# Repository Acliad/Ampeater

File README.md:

# Overview
This project is a 50 W electronic load. The table below outlines the basic specs for the load.

| Description                                 | Spec               |
|---------------------------------------------|--------------------|
| Supply Voltage                              | 12 V               |
| Slew Rate                                   | 10 A/µs        |
| Maximum Current                             | 10 A               |
| Maximum Power Dissipation                   | 50 W               |
| Program Resolution (low range / high range) | 1 mA / 10 mA       |
| Program Accuracy                            | 0.2% $\pm$ 0.2% FS |
| Maximum Overshoot                           | 1%                 |
| Measurement Readout Accuracy                | 0.2% $\pm$ 0.2% FS |

The primary challenge with designing an electronic load is to making it stable over a wide range of load currents and input conditions. This challenges becomes worse when the design demands a fast rise time. The target slew rate for this load is 10 A/µs, which is quite fast. In comparison, the [Keysight EL34243A](https://www.keysight.com/zz/en/assets/3120-1430/data-sheets/EL30000-Series.pdf) has a slew rate of about 5 A/µs. 

This challenge is two-fold. The initial and obvious challenge is the control loop, which is discussed in detail in the [Theory Of Operation](#theory-of-operation) section. Simply, this requires proper compensation to maintain stability and rise time. The more nefarious issue is the issue of input impedance, largely due to the inductance of the wires connecting the load to the source being tested. This inductance is, in general, not known and can vary widely, in the range of 50 nH to 2 uH between short, heavy gauge wire and garden-variety banana cables. This inductance has a large affect on the control loop and can significantly change the rise time and stability of the load. 

Because the current level and slew rate are so large, the slew rate and overshoot specs are defined to be valid for input inductances in the range of 100 nH–roughly 10 cm of 12 AWG wire. This was the assumed input inductance during the design stage. 

# Design and Simulation
## The Control Loop
Figure 1 shows the main control circuit. The main compensation components have been highlighted. Q201 and gate resistors are used to switch the current range between 1 A and 10 A. For this analysis, assume either R211+R212 OR R214 is connected. R202 isolates the output of the opamp from the gate capacitance, which is required for stability. This compensator is known as a [*Type III compensator*](https://www.ti.com/seclit/ml/slup340/slup340.pdf). There are two compensators, each designed to sink up to 0.5/5.0 A. This is done to reduce power dissipation in each transistor.

<p align="center">
 
<figcaption align = "center"><b>Figure 1: Control Loop Circuit</b></figcaption>
</p>

The poles and zeros of the compensator can be set by the compensation components outlined in Figure 1, with equations given in [Switch-mode power converter compensation made easy](https://www.ti.com/seclit/ml/slup340/slup340.pdf).

Figure 2 shows the SPICE simulation setup for the control loop, where the spice models for the TLV9162 were provided by TI and the spice models for the IRF3205 were provided by Infineon. R6 and C4 are used to compensate for the inductance L1. 

<p align="center">
 
<figcaption align = "center"><b>Figure 2: Simulation Schematic</b></figcaption>
</p>

The values for the compensation components were tuned until the desired step response was obtained. Figure 3 below shows the simulated step response to 10 A for RS = 0.2, L1 = 100 nH. The compensation values are given in Figure 1. The overshoot spec is met and the 10% to 90% rise time was measured to be 1.03µs. 

<p align="center">
 
<figcaption align = "center"><b>Figure 3: Simulated Step Response</b></figcaption>
</p>

## Controlling The Control Loop
An STM32L041 was used as the microcontroller for this board. It was chosen for its availability at the time of design (which was during the 2022 parts shortage). It features an on-board 12-bit ADC, which has enough resolution to meet the measurement specs, but the resolution can be further improved using hardware oversampling. 

A DAC is used to set the control voltage for the control loop. The chosen DAC is the ADI AD5452YRM, a fast settling time R2-R DAC. This DAC was chosen as the step response of the DAC needed to be at least as fast as the response of the overall control circuit. The chosen DAC should be more than sufficent for the task. 

Figure 4 shows the DAC arrangement. As noted in the image, the reference voltage is being fed into the current output pin of the DAC and the output voltage is being taken from the Vref pin. R2-R DACs generally allow this arrangement (unless the output is internally buffered), but typically require the reference voltage to be much less than than the supply voltage to overcome the required Vgs of the internal FETs. The ADI datasheet is not clear on how much larger Vcc should be, so the first attempt simply used a 3.3V supply. 

The output impedance of an R2-R DAC in this reverse arrangement is equal to the R value, which is 10k for the AD5452YRM. It is possible that the RC time constant could slow down the output transition, so the traces connecting the DAC to the opamp input should be kept short.
<p align="center">
 
<figcaption align = "center"><b>Figure 4: DAC Schematic Block</b></figcaption>
</p>

## Heatsinking
A large heatsink was chosen to be capable of dissipating at least 50 W with forced air cooling. The thermal calculations were done assuming smooth fin design, however, the chosen heatsink has serrated fins which should significantly improve the heatsinking ability. 

## Human Interfacing
A colored LCD, two pushbuttons, and a rotary encoder with a built-in push button is used to interface with the electronic load. The primary function of the buttons are:
- Output On/Off
- Slew Rate Setting
- Range Selection

The rotary encoder is used to set the load current.

# Results
The final board is shown in Figure 5. All basic DC functions worked including range switching, current measurement, and current sinking up to 10 A. It was found to be stable over the entire range of set current, with some small amount of ringing on the 10 A setting with 2X3ft (6ft ~ 2nH input inductance). 

<p align="center">
 
<figcaption align = "center"><b>Figure 5: Assembled Ampeater</b></figcaption>
</p>

The output was found to be overdamped when two 8 cm lengths of 12 AWG wire were used to connect to the load. The scope capture is shown in Figure 6. The capture is measured across Rsense of one of the control loops with a resistance of ~0.2 Ohms, so 1 V equals 10 A of load current. The capture shows a clearly overdamped response, which makes the load very stable but much slower than desired with a rise time of ~11 µs. To adjust this, the compensation components must be tuned and the measurement performed until the results are acceptable. This is still a TODO item. 

<p align="center">
 
<figcaption align = "center"><b>Figure 6: Scope capture measured across one controller's Rsense</b></figcaption>
</p>

Both the hardware and software are currently in prototype phase and much remains to be done, especially on the software side. However, early results are quite good and all specs appear to be met except the rise time. Tuning of component values will need to be done to ensure this spec is met.

# TODO
- ## Hardware
  - Add output buffer to range select switch
  - Increase reference voltage
  - (Probably) decrease low range current sense resistor
  - Make slightly longer for connectors
  - Add power switch labels
  - Add spots for R6 and C4 (simulation reference designators) compensation resistor/cap
  - Tune compensation values on prototype board to increase rise time. 
- ## Software
  - Investigate a continuos mode ADC sampling that doesn't require polling of every channel for a single channel read
  - Use a faster LCD Library utilizing DMA
  - Add proper return type and error throwing for completion 
  - Use the Vrefint to measure external VDDA for more accurate readings
  - Implement encoder velocity 
  - Implement slew rate limiting
  - Implement a calibration routine to calibrate to resistors 
- ## Documentation
  - Add more discussion on compensator in Theory Of Operation (not currently done do to the absurdity of trying to add equations to GitHub's Markdown)
  - Update images of board

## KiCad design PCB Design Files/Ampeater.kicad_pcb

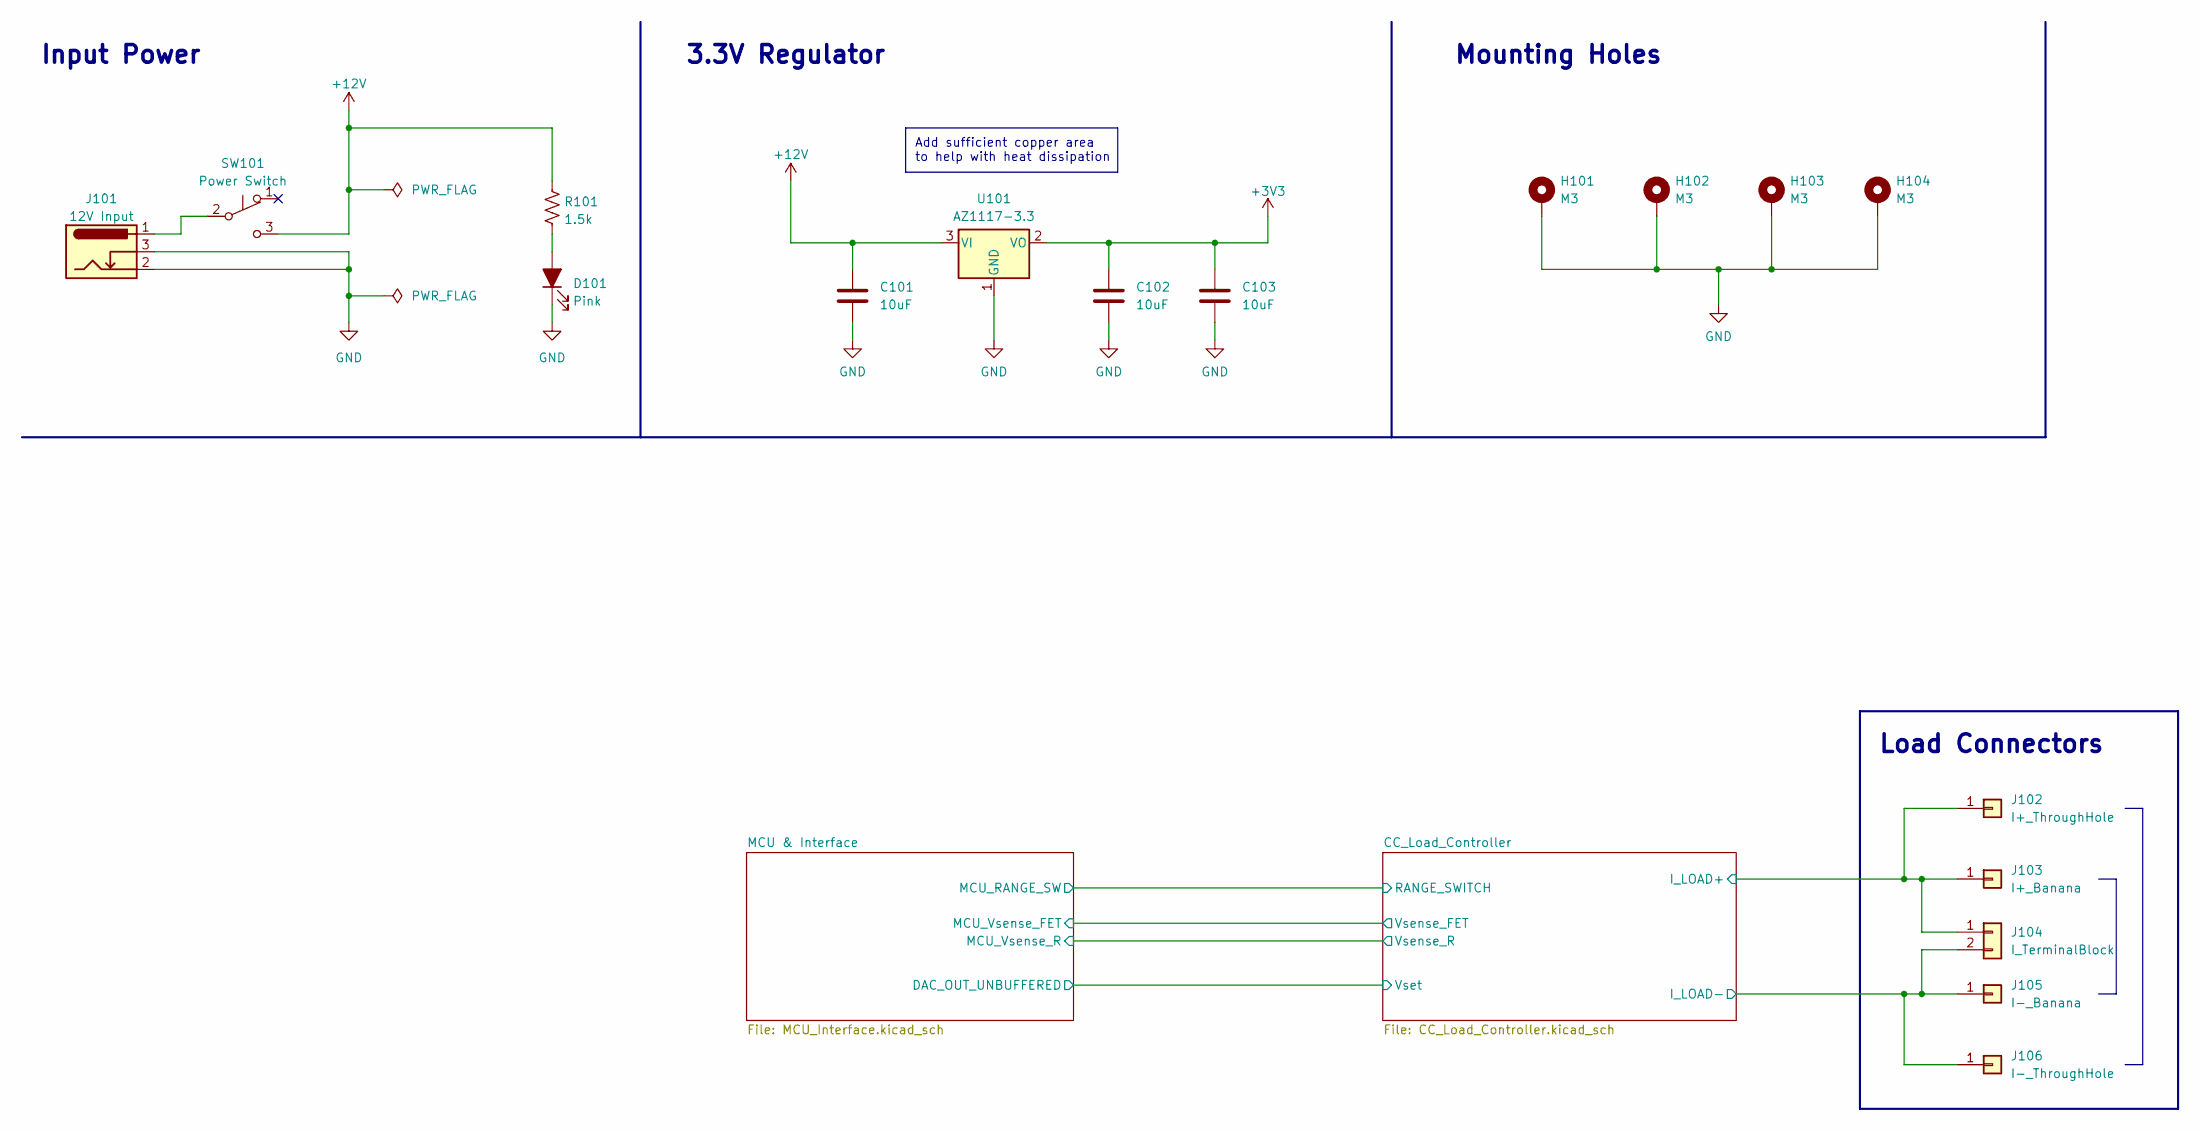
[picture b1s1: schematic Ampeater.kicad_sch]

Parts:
C101, C102, C103: 10uF; C_0603_1608Metric; Digi-Key PN 490-18214-1-ND
D101: Pink; LED_Kingbright_AA3528V_3.5x2.8mm_handsolder
H101, H102, H103, H104: M3; MountingHole_3.2mm_M3_Pad
J101: 12V Input; BarrelJack_CUI_PJ-102AH_Horizontal; Digi-Key PN CP-102AH-ND
J102: I+_ThroughHole; TestPoint_THTPad_D4.0mm_Drill2.0mm
J103: I+_Banana; CalTest_CT3151; Digi-Key PN BKCT3151SP-4-ND
J104: I_TerminalBlock; TerminalBlock_Philmore_TB132_1x02_P5.00mm_Horizontal; Digi-Key PN 732-10955-ND
J105: I-_Banana; CalTest_CT3151; Digi-Key PN BKCT3151SP-6-ND
J106: I-_ThroughHole; TestPoint_THTPad_D4.0mm_Drill2.0mm
R101: 1.5k; R_0603_1608Metric; Digi-Key PN A121524CT-ND
SW101: Power Switch; SW_E-Switch_EG1271_SPDT; Digi-Key PN EG1918-ND
U101: AZ1117-3.3; TO-252-2; Digi-Key PN AZ1117CD-3.3TRG1DICT-ND

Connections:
+3V3: C102.1, C103.1, U101.2 (VO); also elsewhere on the board
+12V: C101.1, R101.1, SW101.3 (C), U101.3 (VI); also elsewhere on the board
/CC_Load_Controller/I_LOAD+: J102.1, J103.1, J104.1; also elsewhere on the board
/CC_Load_Controller/I_LOAD-: J104.2, J105.1, J106.1; also elsewhere on the board
GND: C101.2, C102.2, C103.2, D101.1 (K), H101.1, H102.1, H103.1, H104.1, J101.2, J101.3, U101.1 (GND); also elsewhere on the board
unnamed: D101.2 (A), R101.2
unnamed: J101.1, SW101.2 (B)

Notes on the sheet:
3.3V Regulator
Mounting Holes
Load Connectors
Add sufficient copper area to help with heat dissipation
Input Power

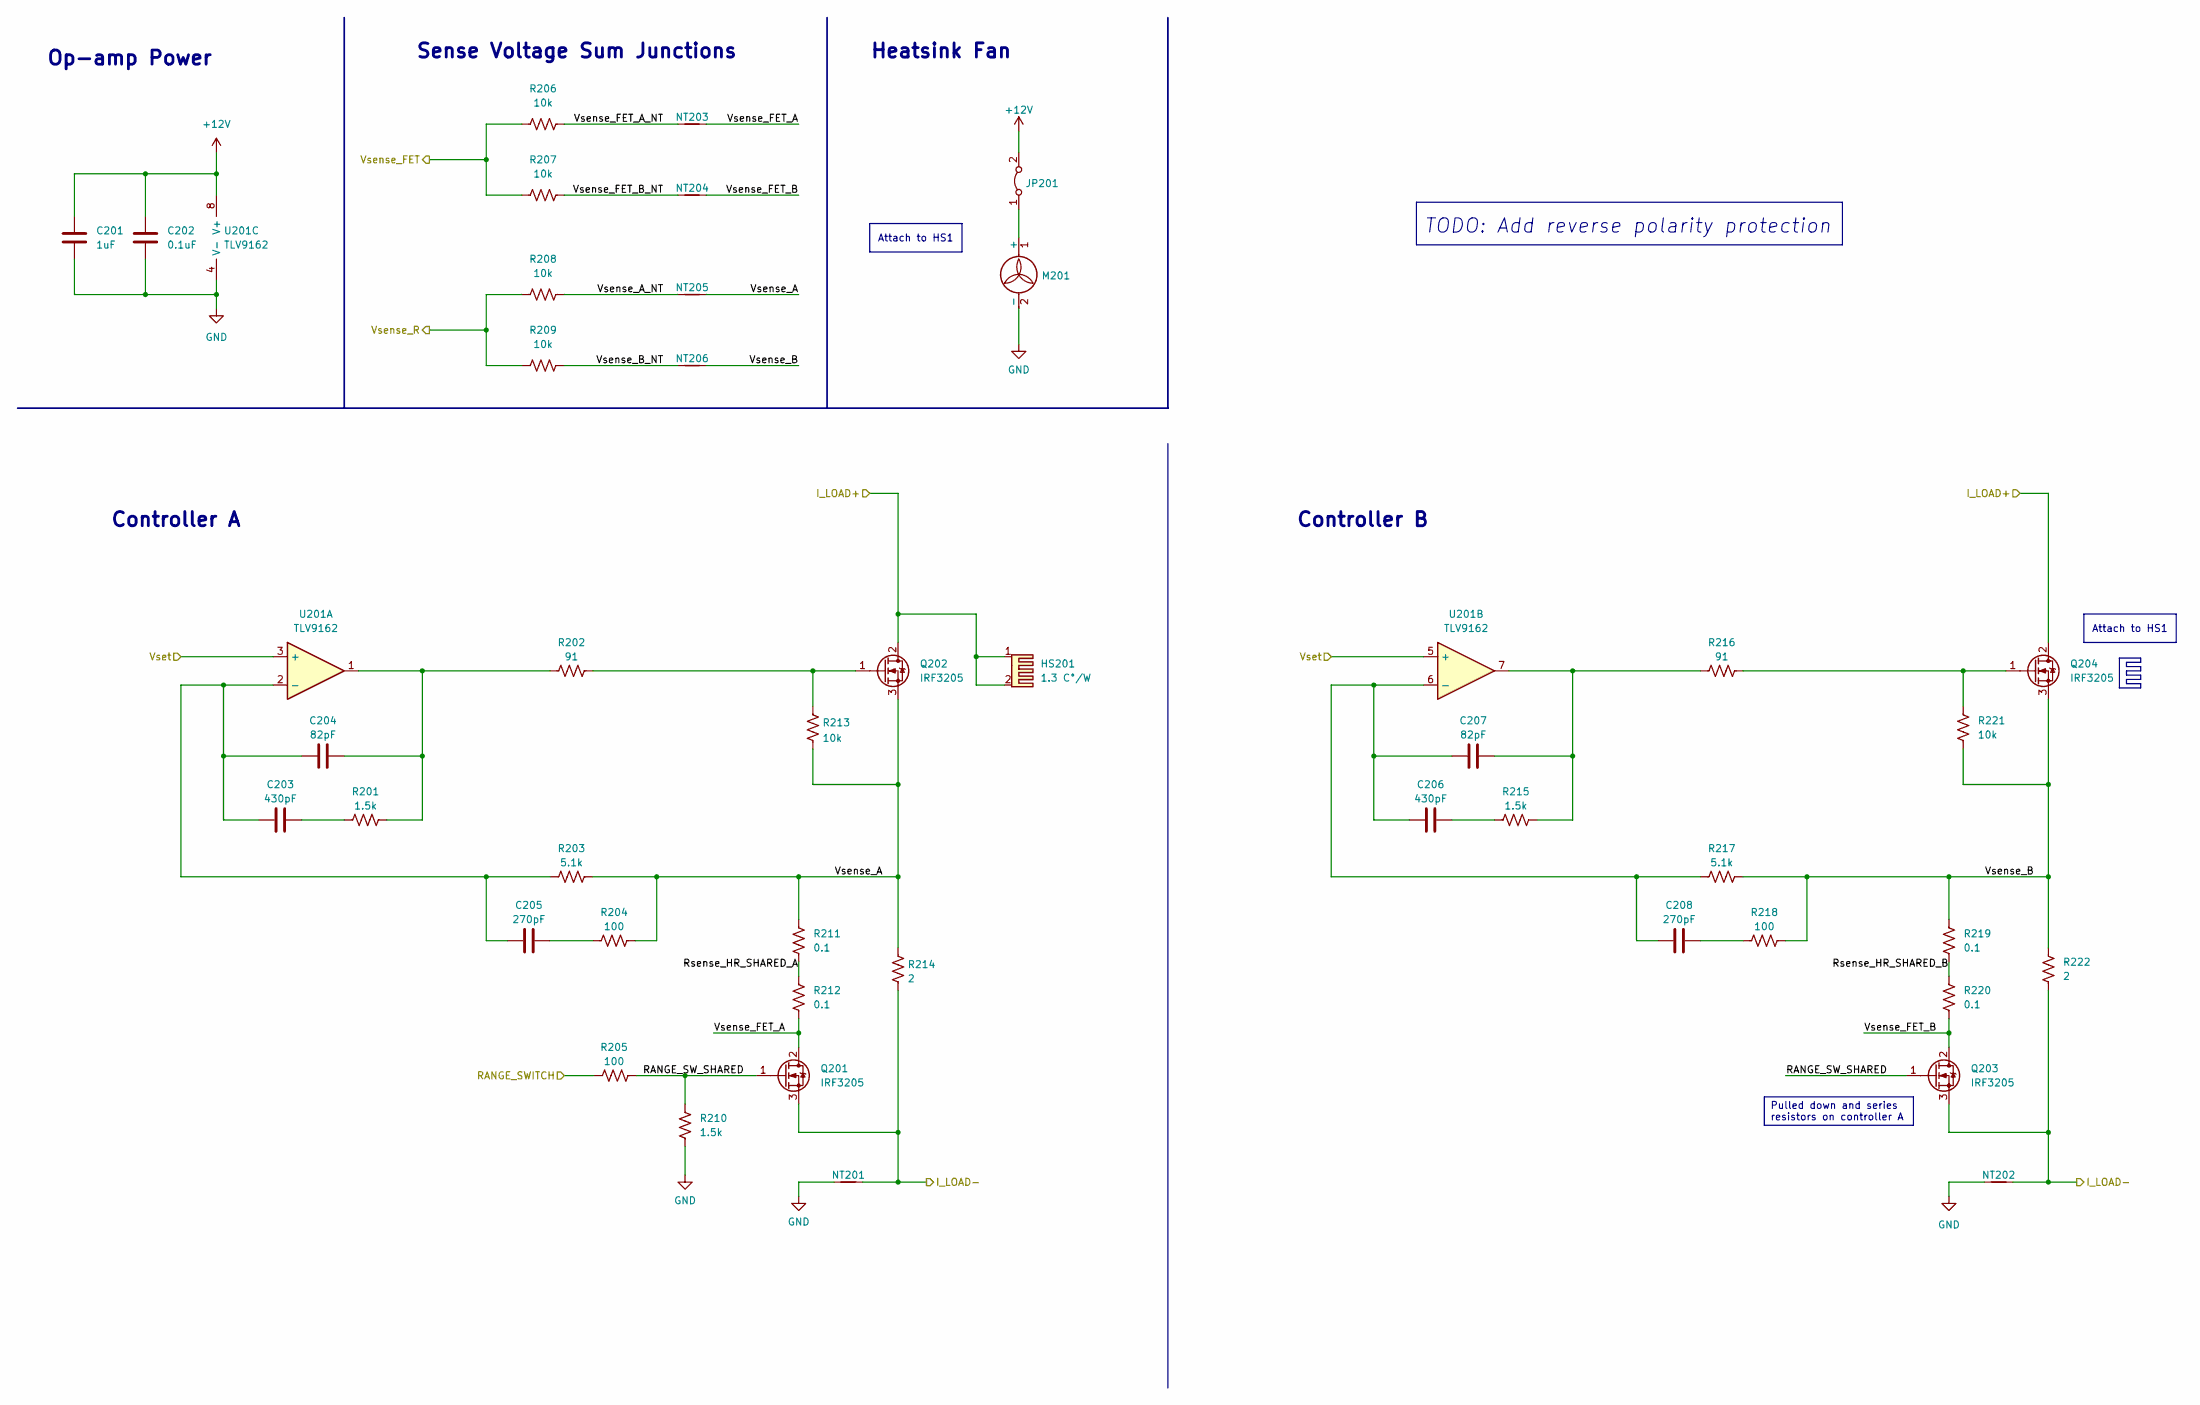
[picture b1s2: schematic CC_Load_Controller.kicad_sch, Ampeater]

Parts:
C201: 1uF; C_0603_1608Metric; Digi-Key PN 1276-1102-1-ND
C202: 0.1uF; C_0603_1608Metric; Digi-Key PN 1276-CL10B104KB8NNNLCT-ND
C203, C206: 430pF; C_0603_1608Metric; Digi-Key PN 490-1442-1-ND
C204, C207: 82pF; C_0603_1608Metric; Digi-Key PN 1276-CL10C820JB81PNDCT-ND
C205, C208: 270pF; C_0603_1608Metric; Digi-Key PN 1276-1256-1-ND
HS201: 1.3 C°/W; Heatsink_HeatsinkUSA_3.00x1.65in_2xDrill5.25mm_TO-220-Mount
JP201: 0603_Jumper; Jumper-2_0603_1608Metric_Trace12mil
M201: Digi-Key PN 455-2247-ND
NT201, NT202: NetTie_GND_I-; NetTie-2_SMD_Pad8.0mils
NT203, NT204, NT205, NT206: (no value)
Q201, Q202, Q203, Q204: IRF3205; TO-220-3_Vertical; Digi-Key PN IRF3205PBF-ND
R201, R210, R215: 1.5k; R_0603_1608Metric; Digi-Key PN A121524CT-ND
R202, R216: 91; R_0603_1608Metric; Digi-Key PN 311-91.0HRCT-ND
R203, R217: 5.1k; R_0603_1608Metric; Digi-Key PN CR0603-FX-5101ELFCT-ND
R204, R205, R218: 100; R_0603_1608Metric; Digi-Key PN A106047CT-ND
R206, R207, R208, R209, R213, R221: 10k; R_0603_1608Metric; Digi-Key PN A106048CT-ND
R211, R212, R219, R220: 0.1; Rohm_GMR100_B6.40x3.20mm; Digi-Key PN 511-1692-1-ND
R214, R222: 2; R_2512_6332Metric; Digi-Key PN 738-CSRT2512FT2R00-UPCT-ND
U201: TLV9162; SOT-23-8; Digi-Key PN TLV9162IDDFR

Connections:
+12V: C201.1, C202.1, JP201.2 (B), U201.8 (V+); also elsewhere on the board
/CC_Load_Controller/I_LOAD+: HS201.1, HS201.2, Q202.2 (D), Q204.2 (D); also elsewhere on the board
/CC_Load_Controller/I_LOAD-: NT201.2, NT202.2, Q201.3 (S), Q203.3 (S), R214.1, R222.1; also elsewhere on the board
/CC_Load_Controller/RANGE_SW_SHARED: Q201.1 (G), Q203.1 (G), R205.2, R210.2
/CC_Load_Controller/Rsense_HR_SHARED_A: R211.1, R212.2
/CC_Load_Controller/Rsense_HR_SHARED_B: R219.1, R220.2
/CC_Load_Controller/Vsense_A: NT205.2, Q202.3 (S), R203.2, R204.2, R211.2, R213.1, R214.2
/CC_Load_Controller/Vsense_A_NT: NT205.1, R208.1
/CC_Load_Controller/Vsense_B: NT206.2, Q204.3 (S), R217.2, R218.2, R219.2, R221.1, R222.2
/CC_Load_Controller/Vsense_B_NT: NT206.1, R209.1
/CC_Load_Controller/Vsense_FET: R206.2, R207.2; also elsewhere on the board
/CC_Load_Controller/Vsense_FET_A: NT203.2, Q201.2 (D), R212.1
/CC_Load_Controller/Vsense_FET_A_NT: NT203.1, R206.1
/CC_Load_Controller/Vsense_FET_B: NT204.2, Q203.2 (D), R220.1
/CC_Load_Controller/Vsense_FET_B_NT: NT204.1, R207.1
/CC_Load_Controller/Vsense_R: R208.2, R209.2; also elsewhere on the board
/CC_Load_Controller/Vset: U201.3 (+), U201.5 (+); also elsewhere on the board
/MCU & Interface/MCU_RANGE_SW: R205.1; also elsewhere on the board
GND: C201.2, C202.2, M201.2 (-), NT201.1, NT202.1, R210.1, U201.4 (V-); also elsewhere on the board
unnamed: C203.1, C204.1, C205.1, R203.1, U201.2 (-)
unnamed: C203.2, R201.1
unnamed: C204.2, R201.2, R202.1, U201.1
unnamed: C205.2, R204.1
unnamed: C206.1, C207.1, C208.1, R217.1, U201.6 (-)
unnamed: C206.2, R215.1
unnamed: C207.2, R215.2, R216.1, U201.7
unnamed: C208.2, R218.1
unnamed: JP201.1 (A), M201.1 (+)
unnamed: Q202.1 (G), R202.2, R213.2
unnamed: Q204.1 (G), R216.2, R221.2

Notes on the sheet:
Heatsink Fan
Pulled down and series resistors on controller A
Attach to HS1
Op-amp Power
Controller A
TODO: Add reverse polarity protection
Sense Voltage Sum Junctions
Controller B

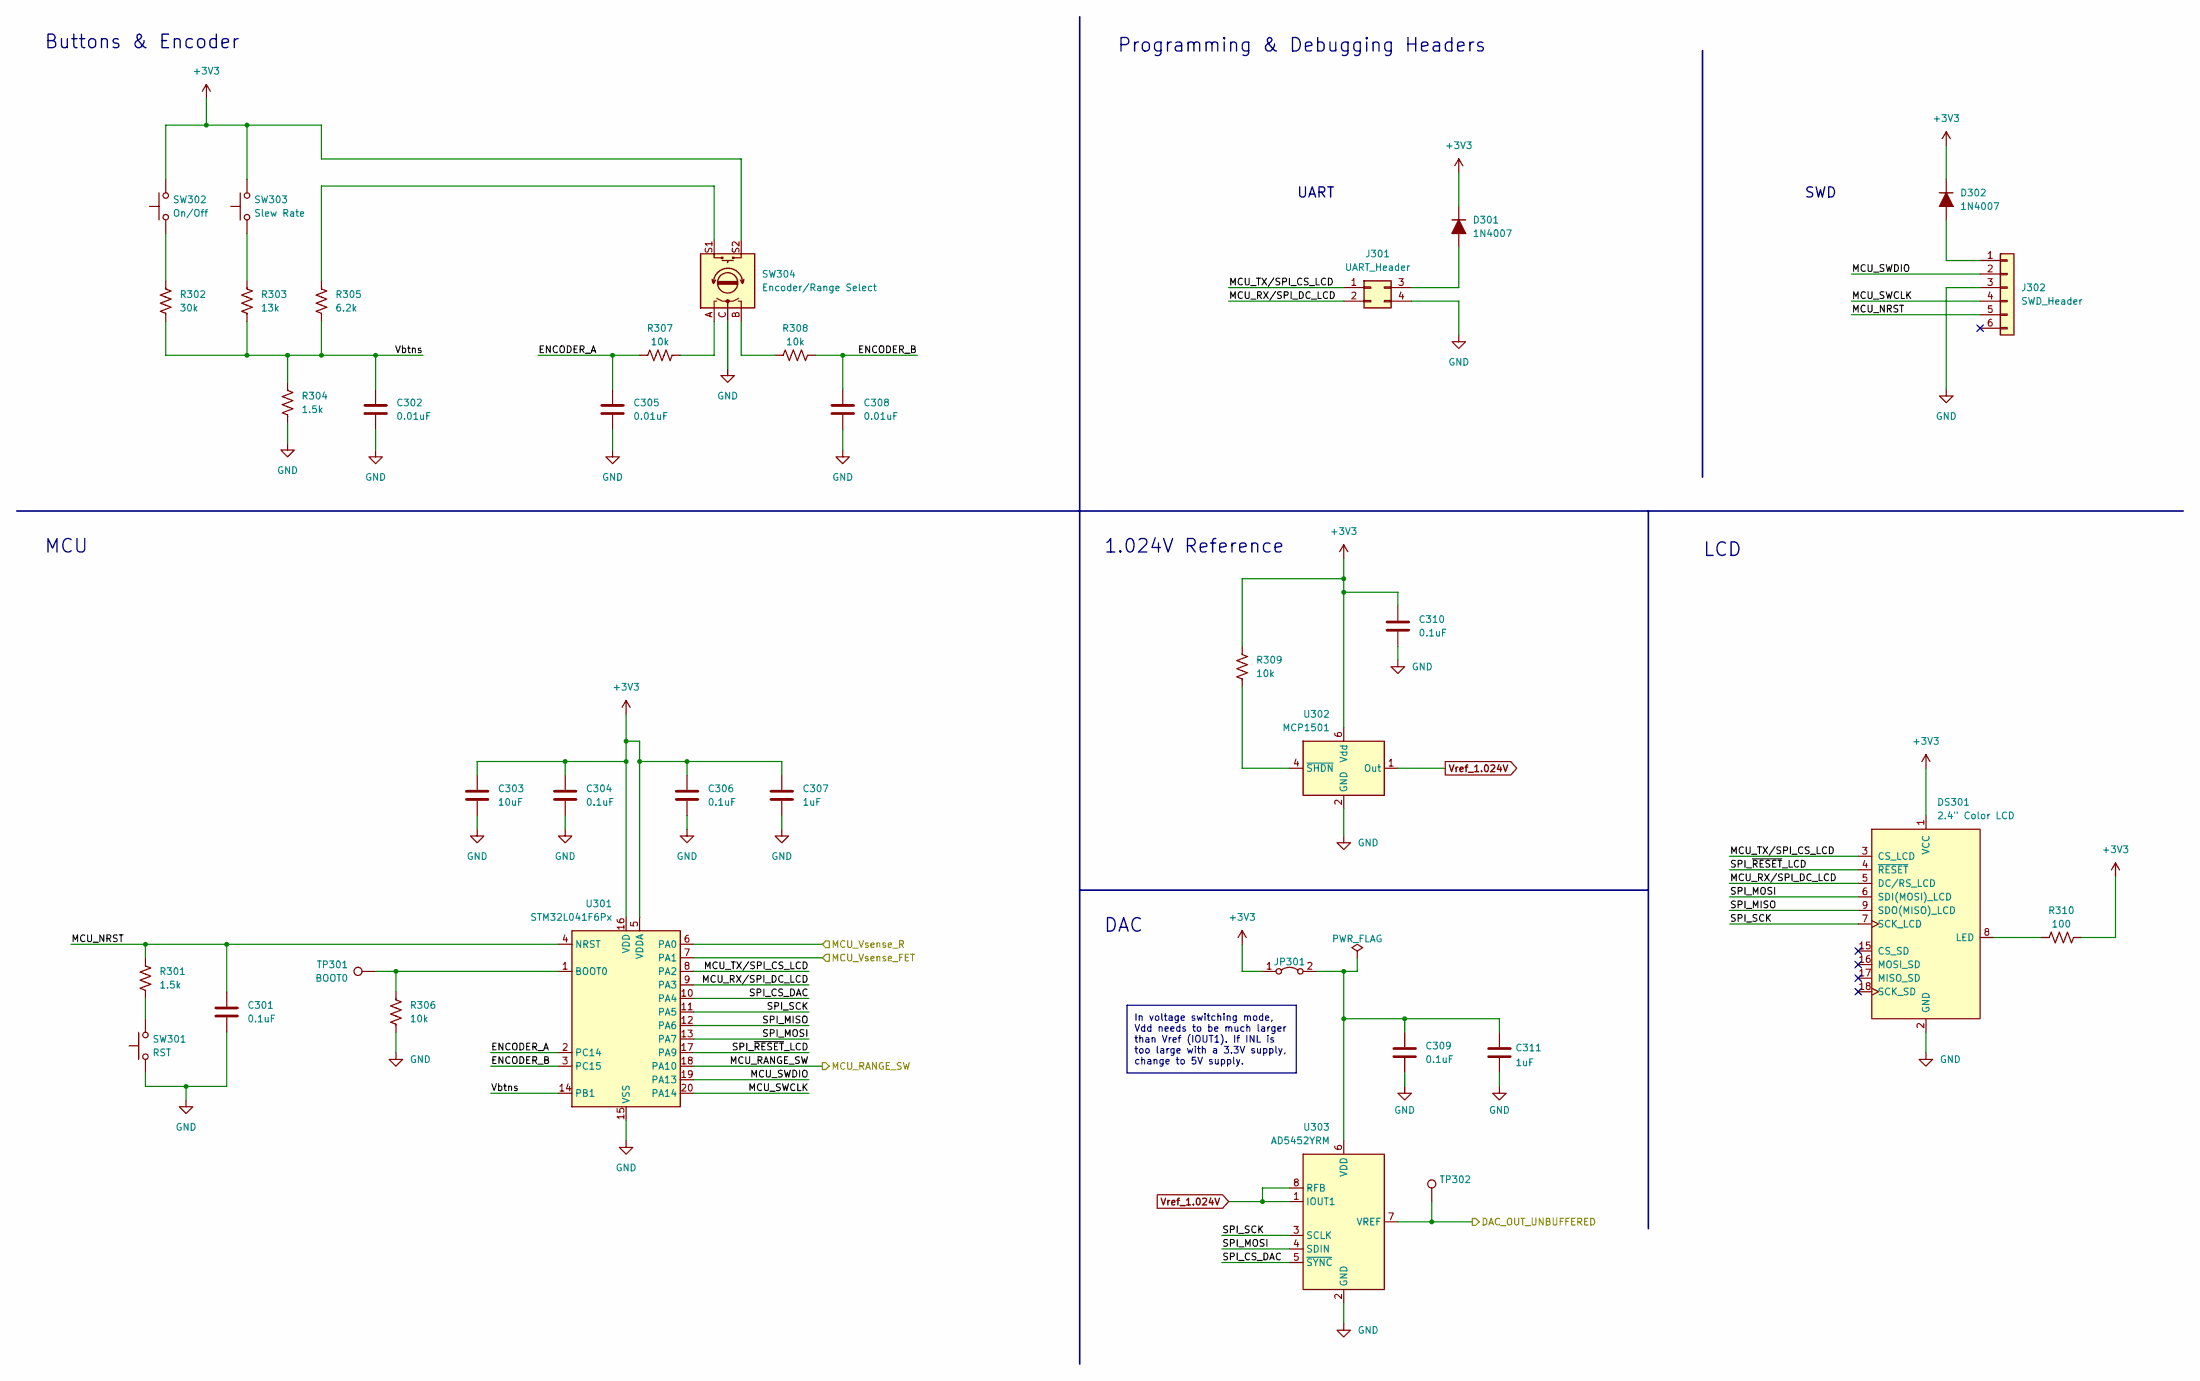
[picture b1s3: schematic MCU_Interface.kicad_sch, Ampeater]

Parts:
C301, C304, C306, C309, C310: 0.1uF; C_0603_1608Metric; Digi-Key PN 1276-CL10B104KB8NNNLCT-ND
C302, C305, C308: 0.01uF; C_0603_1608Metric; Digi-Key PN 1276-1009-1-ND
C303: 10uF; C_0603_1608Metric; Digi-Key PN 490-18214-1-ND
C307, C311: 1uF; C_0603_1608Metric; Digi-Key PN 1276-1102-1-ND
D301, D302: 1N4007; D_SOD-123F; Digi-Key PN 1655-1N4007FLCT-ND
DS301: 2.4" Color LCD; LCD-Generic-2.4in_77.18x42.72mm_ReducedCourtyard
J301: UART_Header; PinHeader_2x02_P2.54mm_Horizontal; Digi-Key PN 2057-PH2RA-04-UA-ND
J302: SWD_Header; PinHeader_1x06_P2.54mm_Horizontal; Digi-Key PN 2057-PH1RA-06-UA-ND
JP301: DAC_Jumper; SolderJumper-2_P1.3mm_Bridged_RoundedPad1.0x1.5mm
R301, R304: 1.5k; R_0603_1608Metric; Digi-Key PN A121524CT-ND
R302: 30k; R_0603_1608Metric; Digi-Key PN CR0603-FX-3002ELFCT-ND
R303: 13k; R_0603_1608Metric; Digi-Key PN CR0603-FX-1302ELFCT-ND
R305: 6.2k; R_0603_1608Metric; Digi-Key PN 13-RC0603FR-136K2LCT-ND
R306, R307, R308, R309: 10k; R_0603_1608Metric; Digi-Key PN A106048CT-ND
R310: 100; R_0603_1608Metric; Digi-Key PN A106047CT-ND
SW301: RST; SW-PUSH-6x3.5mm_CK-PTS636SL43x_HandSolder; Digi-Key PN CKN12309-1-ND
SW302: On/Off; SW_PUSH-12mm_Wuerth-430476085716_HandSolder; Digi-Key PN 732-13655-1-ND
SW303: Slew Rate; SW_PUSH-12mm_Wuerth-430476085716_HandSolder; Digi-Key PN 732-13655-1-ND
SW304: Encoder/Range Select; RotaryEncoder_Alps_EC12E-Switch_Vertical_H20mm; Digi-Key PN PEC12R-4217F-S0024-ND
TP301: BOOT0; TestPoint_THTPad_D2.5mm_Drill1.2mm
TP302: (no value)
U301: STM32L041F6Px; TSSOP-20_4.4x6.5mm_P0.65mm; Digi-Key PN 497-16810-ND
U302: MCP1501; SOT-23-6; Digi-Key PN MCP1501T-10E/CHYCT-ND
U303: AD5452YRM; MSOP-8_3x3mm_P0.65mm; Digi-Key PN AD5452YRMZ-REEL7CT-ND

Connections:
+3V3: C303.1, C304.1, C306.1, C307.1, C310.1, D301.1 (K), D302.1 (K), DS301.1 (VCC), JP301.1 (A), R309.1, R310.2, SW302.2, SW303.2, SW304.S2, U301.5 (VDDA), U301.16 (VDD), U302.6 (Vdd); also elsewhere on the board
/CC_Load_Controller/Vsense_FET: U301.7 (PA1); also elsewhere on the board
/CC_Load_Controller/Vsense_R: U301.6 (PA0); also elsewhere on the board
/CC_Load_Controller/Vset: TP302.1, U303.7 (VREF); also elsewhere on the board
/MCU & Interface/ENCODER_A: C305.1, R307.1, U301.2 (PC14)
/MCU & Interface/ENCODER_B: C308.1, R308.2, U301.3 (PC15)
/MCU & Interface/MCU_NRST: C301.1, J302.5, R301.1, U301.4 (NRST)
/MCU & Interface/MCU_RANGE_SW: U301.18 (PA10); also elsewhere on the board
/MCU & Interface/MCU_RX/SPI_DC_LCD: DS301.5 (DC/RS_LCD), J301.2, U301.9 (PA3)
/MCU & Interface/MCU_SWCLK: J302.4, U301.20 (PA14)
/MCU & Interface/MCU_SWDIO: J302.2, U301.19 (PA13)
/MCU & Interface/MCU_TX/SPI_CS_LCD: DS301.3 (CS_LCD), J301.1, U301.8 (PA2)
/MCU & Interface/SPI_CS_DAC: U301.10 (PA4), U303.5 (~SYNC)
/MCU & Interface/SPI_MISO: DS301.9 (SDO(MISO)_LCD), U301.12 (PA6)
/MCU & Interface/SPI_MOSI: DS301.6 (SDI(MOSI)_LCD), U301.13 (PA7), U303.4 (SDIN)
/MCU & Interface/SPI_SCK: DS301.7 (SCK_LCD), U301.11 (PA5), U303.3 (SCLK)
/MCU & Interface/SPI_~RESET_LCD: DS301.4 (~RESET), U301.17 (PA9)
/MCU & Interface/Vbtns: C302.1, R302.2, R303.2, R304.1, R305.2, U301.14 (PB1)
GND: C301.2, C302.2, C303.2, C304.2, C305.2, C306.2, C307.2, C308.2, C309.2, C310.2, C311.2, DS301.2 (GND), J301.4, J302.3, R304.2, R306.2, SW301.1, SW304.C, U301.15 (VSS), U302.2 (GND), U302.3 (GND), U302.5 (GND), U303.2 (GND); also elsewhere on the board
unnamed: C309.1, C311.1, JP301.2 (B), U303.6 (VDD)
unnamed: D301.2 (A), J301.3
unnamed: D302.2 (A), J302.1
unnamed: DS301.8 (LED), R310.1
unnamed: R301.2, SW301.2
unnamed: R302.1, SW302.1
unnamed: R303.1, SW303.1
unnamed: R305.1, SW304.S1
unnamed: R306.1, TP301.1, U301.1 (BOOT0)
unnamed: R307.2, SW304.A
unnamed: R308.1, SW304.B
unnamed: R309.2, U302.4 (~SHDN)
Vref_1.024V: U302.1 (Out), U303.1 (IOUT1), U303.8 (RFB)

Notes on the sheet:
Buttons & Encoder
SWD
UART
LCD
1.024V Reference
Programming & Debugging Headers
MCU
In voltage switching mode, Vdd needs to be much larger than Vref (IOUT1). If INL is too large with a 3.3V supply, change to 5V supply.
DAC

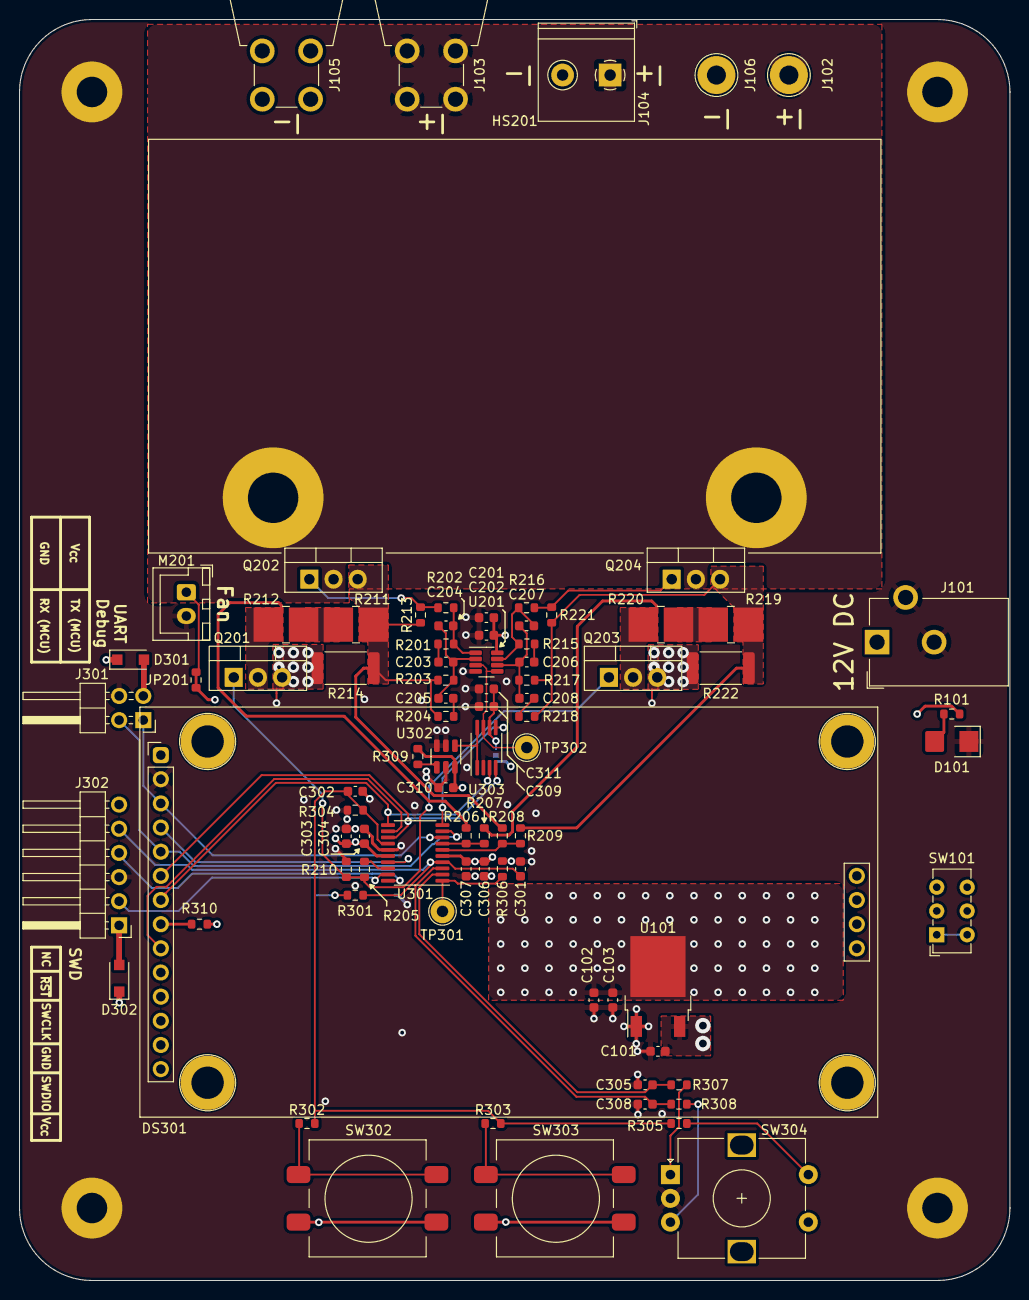
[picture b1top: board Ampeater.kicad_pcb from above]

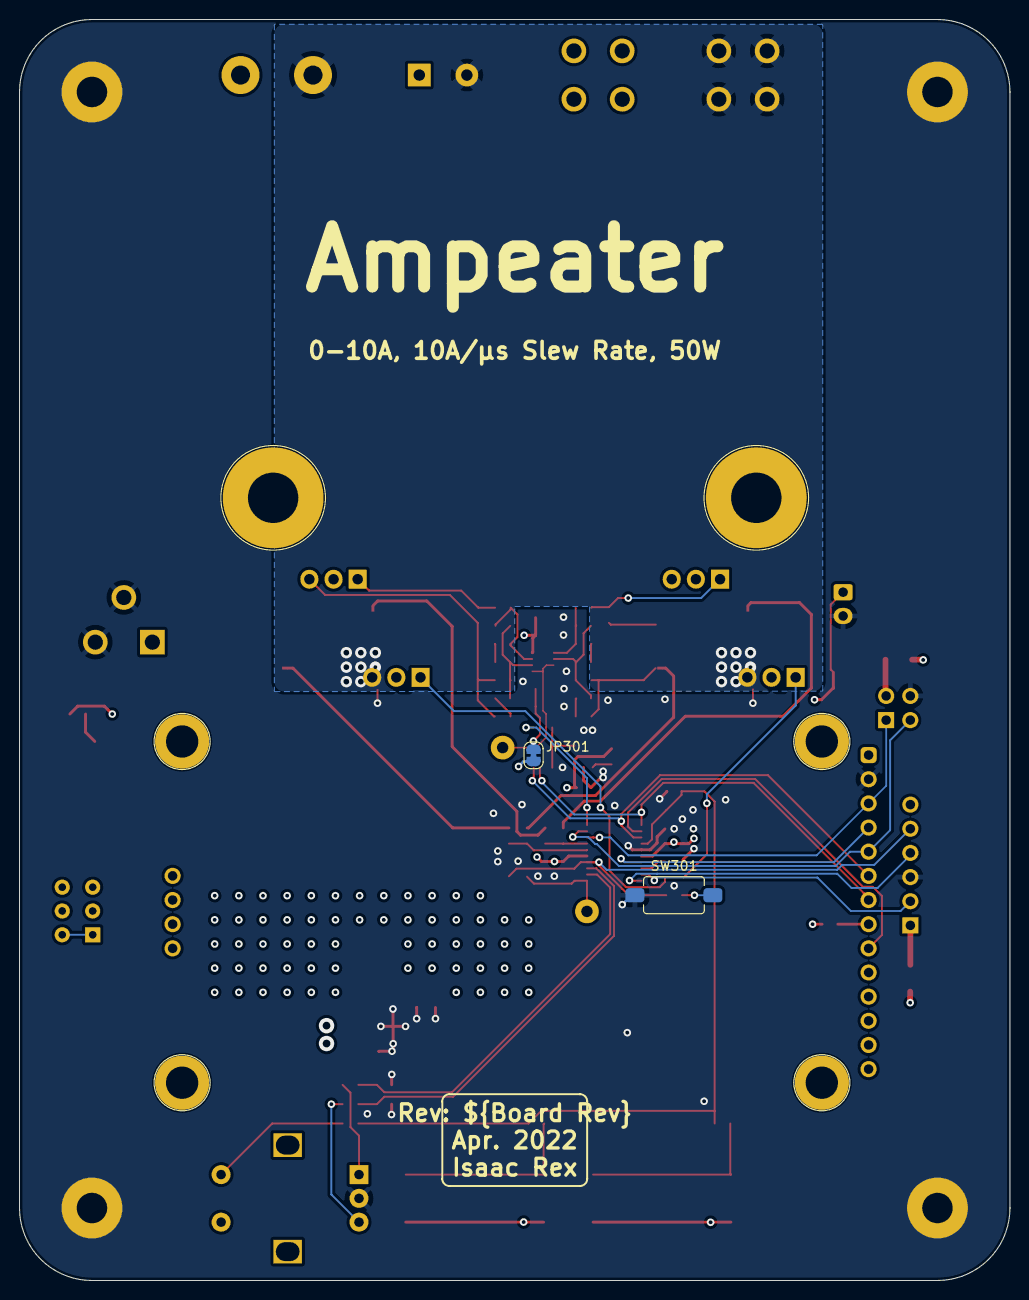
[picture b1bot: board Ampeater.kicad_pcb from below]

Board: 4 copper layers, 104.1 x 132.6 mm, 97 parts (2 on the bottom side), 59 nets.

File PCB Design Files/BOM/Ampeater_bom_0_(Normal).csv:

References,Value,Digi-Key PN,Quantity Per PCB,Footprint,Datasheet
"C204, C207",82pF,1276-CL10C820JB81PNDCT-ND,2,C_0603_1608Metric,~
"C205, C208",270pF,1276-1256-1-ND,2,C_0603_1608Metric,~
"C203, C206",430pF,490-1442-1-ND,2,C_0603_1608Metric,~
"C302, C305, C308",0.01uF,1276-1009-1-ND,3,C_0603_1608Metric,~
"C202, C301, C304, C306, C309, C310",0.1uF,1276-CL10B104KB8NNNLCT-ND,6,C_0603_1608Metric,~
"C201, C307, C311",1uF,1276-1102-1-ND,3,C_0603_1608Metric,~
"C101, C102, C103, C303",10uF,490-18214-1-ND,4,C_0603_1608Metric,~
"D301, D302",1N4007,1655-1N4007FLCT-ND,2,D_SOD-123F,~
DS301,"2.4"" Color LCD",,1,,
HS201,1.3 C°/W,,1,,~
J101,12V Input,CP-102AH-ND,1,BarrelJack_CUI_PJ-102AH_Horizontal,~
J103,I+_Banana,BKCT3151SP-4-ND,1,CalTest_CT3151,~
J105,I-_Banana,BKCT3151SP-6-ND,1,CalTest_CT3151,~
J104,I_TerminalBlock,732-10955-ND,1,TerminalBlock_Philmore_TB132_1x02_P5.00mm_Horizontal,~
J302,SWD_Header,2057-PH1RA-06-UA-ND,1,PinHeader_1x06_P2.54mm_Horizontal,~
J301,UART_Header,2057-PH2RA-04-UA-ND,1,PinHeader_2x02_P2.54mm_Horizontal,~
JP201,0603_Jumper,,1,Jumper-2_0603_1608Metric_Trace12mil,~
M201,Fan,455-2247-ND,1,JST_XH_B2B-XH-AM_1x02_P2.50mm_Vertical,~
NT201,NetTie_GND_I-,,1,NetTie-2_SMD_Pad8.0mils,~
NT202,NetTie_GND_I-,,1,NetTie-2_SMD_Pad8.0mils,~
"Q201, Q202, Q203, Q204",IRF3205,IRF3205PBF-ND,4,R_0603_1608Metric,~
"R211, R212, R219, R220",0.1,511-1692-1-ND,4,Rohm_GMR100_B6.40x3.20mm,~
"R214, R222",2,738-CSRT2512FT2R00-UPCT-ND,2,R_2512_6332Metric,~
"R202, R216",91,311-91.0HRCT-ND,2,R_0603_1608Metric,~
"R204, R205, R218, R310",100,A106047CT-ND,4,R_0603_1608Metric,~
"R201, R210, R215, R301, R304",1.5k,A121524CT-ND,5,R_0603_1608Metric,~
"R203, R217",5.1k,CR0603-FX-5101ELFCT-ND,2,R_0603_1608Metric,~
R305,6.2k,13-RC0603FR-136K2LCT-ND,1,R_0603_1608Metric,~
"R206, R207, R208, R209, R213, R221, R306, R307, R308, R309",10k,A106048CT-ND,10,R_0603_1608Metric,~
R303,13k,CR0603-FX-1302ELFCT-ND,1,R_0603_1608Metric,~
R302,30k,CR0603-FX-3002ELFCT-ND,1,R_0603_1608Metric,~
SW304,Encoder/Range Select,PEC12R-4217F-S0024-ND,1,RotaryEncoder_Alps_EC12E-Switch_Vertical_H20mm,~
SW302,On/Off,732-13655-1-ND,1,SW_PUSH-12mm_Wuerth-430476085716_HandSolder,~
SW101,Power Switch,EG1918-ND,1,,~
SW301,RST,CKN12309-1-ND,1,SW_PUSH-12mm_Wuerth-430476085716_HandSolder,~
SW303,Slew Rate,732-13655-1-ND,1,SW_PUSH-12mm_Wuerth-430476085716_HandSolder,~
U303,AD5452YRM,AD5452YRMZ-REEL7CT-ND,1,MSOP-8_3x3mm_P0.65mm,https://www.analog.com/media/en/technical-documentation/data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
U101,AZ1117-3.3,AZ1117CD-3.3TRG1DICT-ND,1,TO-252-2,https://www.diodes.com/assets/Datasheets/AZ1117.pdf
U302,MCP1501,MCP1501T-10E/CHYCT-ND,1,SOT-23-6,http://ww1.microchip.com/downloads/en/DeviceDoc/20005474E.pdf
U301,STM32L041F6Px,497-16810-ND,1,TSSOP-20_4.4x6.5mm_P0.65mm,http://www.st.com/st-web-ui/static/active/en/resource/techni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
U201,TLV9162,TLV9162IDDFR,1,SOT-23-8,~





Component Groups:,41
Component Count:,82
Fitted Components:,82
Number of PCBs:,1
Total components:,82
Schematic Version:,0
Schematic Date:,2022-03-14
PCB Variant:,normal
BoM Date:,"Wednesday, March 16, 2022 at 10:53:04 AM"
Schematic Source:,Ampeater.kicad_sch
KiCad Version:,Eeschema (6.0.2-0)

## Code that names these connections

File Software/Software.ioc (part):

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Mcu.Name=STM32L041F6Px
Mcu.Package=TSSOP20
Mcu.UserName=STM32L041F6Px
PA0-CK_IN.GPIOParameters=GPIO_Label
PA0-CK_IN.GPIO_Label=Vsense_R
PA0-CK_IN.Mode=IN0
PA0-CK_IN.Signal=ADC_IN0
PA1.GPIOParameters=GPIO_Label
PA1.GPIO_Label=Vsense_FET
PA1.Mode=IN1
PA1.Signal=ADC_IN1
PA10.GPIOParameters=GPIO_Label
PA10.GPIO_Label=RANGE_SW
PA10.Signal=GPIO_Output
PA13.Mode=Serial_Wire
PA13.Signal=SYS_SWDIO
PA14.Mode=Serial_Wire
PA14.Signal=SYS_SWCLK
PA2.GPIOParameters=GPIO_Label
PA2.GPIO_Label=UART_TX_SPI_CS_LCD
PA2.Mode=Asynchronous
PA2.Signal=USART2_TX
PA3.GPIOParameters=GPIO_Label
PA3.GPIO_Label=UART_RX_SPI_DC_LCD
PA3.Mode=Asynchronous
PA3.Signal=USART2_RX
PA4.GPIOParameters=GPIO_Speed,GPIO_Label
PA4.GPIO_Label=SPI_CS_DAC
PA4.GPIO_Speed=GPIO_SPEED_FREQ_VERY_HIGH
PA4.Signal=GPIO_Output
PA5.GPIOParameters=GPIO_Label
PA5.GPIO_Label=SPI_SCK
PA5.Mode=Full_Duplex_Master
PA5.Signal=SPI1_SCK
PA6.GPIOParameters=GPIO_Label
PA6.GPIO_Label=SPI_MISO
PA6.Mode=Full_Duplex_Master
PA6.Signal=SPI1_MISO
PA7.GPIOParameters=GPIO_Label
PA7.GPIO_Label=SPI_MOSI
PA7.Mode=Full_Duplex_Master
PA7.Signal=SPI1_MOSI
PA9.GPIOParameters=GPIO_Speed,GPIO_Label
PA9.GPIO_Label=SPI_nRST_LCD
PA9.GPIO_Speed=GPIO_SPEED_FREQ_VERY_HIGH
PA9.Signal=GPIO_Output
PB1.GPIOParameters=GPIO_Label
PB1.GPIO_Label=Vbtns
PB1.Mode=IN9
PB1.Signal=ADC_IN9
PC14-OSC32_IN.GPIOParameters=GPIO_PuPd,GPIO_Label,GPIO_ModeDefaultEXTI
PC14-OSC32_IN.GPIO_Label=ENCODER_A
PC14-OSC32_IN.GPIO_ModeDefaultEXTI=GPIO_MODE_IT_RISING_FALLING
PC14-OSC32_IN.GPIO_PuPd=GPIO_PULLUP
PC14-OSC32_IN.Signal=GPXTI14
PC15-OSC32_OUT.GPIOParameters=GPIO_PuPd,GPIO_Label
PC15-OSC32_OUT.GPIO_Label=ENCODER_B
PC15-OSC32_OUT.GPIO_PuPd=GPIO_PULLUP
PC15-OSC32_OUT.Signal=GPXTI15
RCC.HSE_VALUE=8000000
RCC.SYSCLKFreq_VALUE=16000000
RCC.SYSCLKSource=RCC_SYSCLKSOURCE_HSI
board=custom

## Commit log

2022-03-28 Adding files after making repo
2022-04-10 Finished board layout
2022-04-23 Added fan shroud 3D model and heatsink drawing
2022-05-14 Updated fan shroud files
2022-05-14 Added initial prototype software
2022-05-15 Added initial documenation
2022-05-15 Updated simulation files
2023-12-12 Fixed LOW/HIGH range issue on boot
    Fixed an issue that caused Ampeater to display LOW range but actually be
    in HIGH range on boot.
